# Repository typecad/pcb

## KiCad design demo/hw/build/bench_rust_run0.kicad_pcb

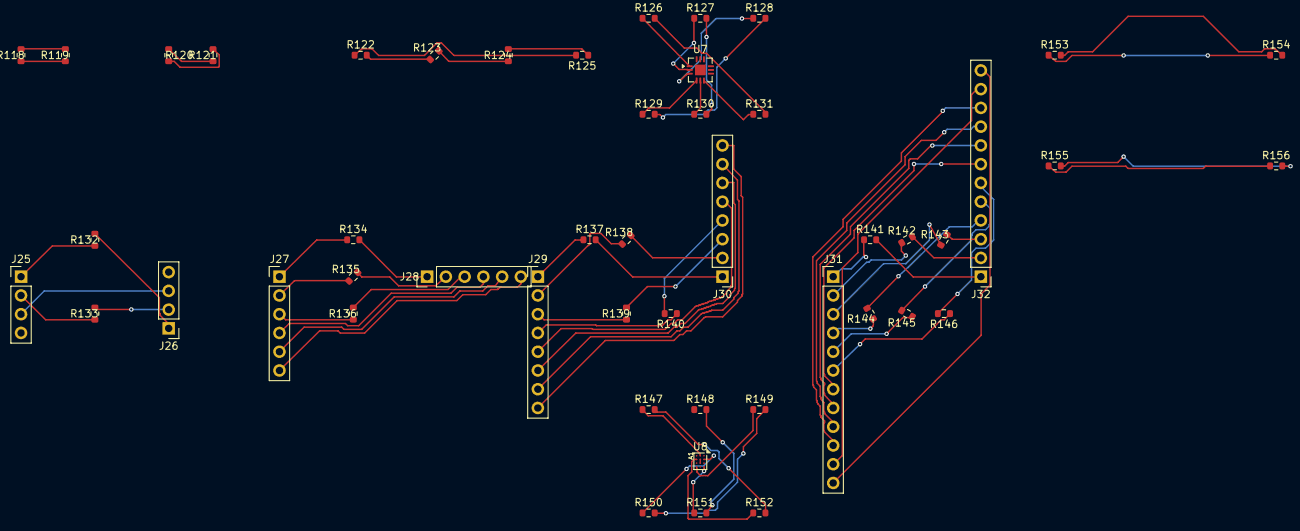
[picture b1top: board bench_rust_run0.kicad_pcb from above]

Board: 0 copper layers, 49 parts (0 on the bottom side), 74 nets.

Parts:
J25, J26: PinHeader_1x04_P2.54mm_Vertical
J27, J28: PinHeader_1x06_P2.54mm_Vertical
J29, J30: PinHeader_1x08_P2.54mm_Vertical
J31, J32: PinHeader_1x12_P2.54mm_Vertical
R118, R119, R120, R121, R122, R123, R124, R125, R126, R127, R128, R129, R130, R131, R132, R133, R134, R135, R136, R137, R138, R139, R140, R141, R142, R143, R144, R145, R146, R147, R148, R149, R150, R151, R152, R153, R154, R155, R156: R_0603_1608Metric
U7: QFN-12-1EP_3x3mm_P0.5mm_EP1.45x1.45mm
U8: Texas_DSBGA-12_1.36x1.86mm_Layout3x4_P0.5mm

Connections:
test1_1: R118.1, R119.1
test1_2: R118.2, R119.2
test2_1: R120.1, R121.1
test2_2: R120.2, R121.2
test3_1: R122.2, R123.1
test3_2: R123.2, R124.1
test3_3: R124.2, R125.1
test3_4: R122.1, R125.2
test4_1: R126.1, U7.1
test4_2: R127.1, U7.2
test4_3: R128.1, U7.3
test4_4: R129.1, U7.4
test4_5: R130.1, U7.5
test4_6: R131.1, U7.6
test4_7: R126.2, R131.2
test4_8: R127.2, R130.2
test4_9: R128.2, R129.2
test5_1: J25.1, R132.1
test5_2: J26.1, R132.2
test5_3: J25.2, R133.1
test5_4: J26.2, R133.2
test5_5: J25.3, J26.3
test6_1: J27.1, R134.1
test6_2: J28.1, R134.2
test6_3: J27.2, R135.1
test6_4: J28.2, R135.2
test6_5: J27.3, R136.1
test6_6: J28.3, R136.2
test6_7: J27.4, J28.4
test6_8: J27.5, J28.5
test6_9: J27.6, J28.6
test7_1: J29.1, R137.1
test7_2: J30.1, R137.2
test7_3: J29.2, R138.1
test7_4: J30.2, R138.2
test7_5: J29.3, R139.1
test7_6: J30.3, R139.2
test7_7: J29.4, R140.1
test7_8: J30.4, R140.2
test7_9: J29.5, J30.5
test7_10: J29.6, J30.6
test7_11: J29.7, J30.7
test7_12: J29.8, J30.8
test8_1: J31.1, R141.1
test8_2: J32.1, R141.2
test8_3: J31.2, R142.1
test8_4: J32.2, R142.2
test8_5: J31.3, R143.1
test8_6: J32.3, R143.2
test8_7: J31.4, R144.1
test8_8: J32.4, R144.2
test8_9: J31.5, R145.1
test8_10: J32.5, R145.2
test8_11: J31.6, R146.1
test8_12: J32.6, R146.2
test8_13: J31.7, J32.7
test8_14: J31.8, J32.8
test8_15: J31.9, J32.9
test8_16: J31.10, J32.10
test8_17: J31.11, J32.11
test8_18: J31.12, J32.12
test9_1: R147.1, U8.A2
test9_2: U8.B2, U8.C2
test9_3: R149.1, U8.D1
test9_4: R150.1, U8.B3
test9_5: R151.1, U8.D3
test9_6: R152.1, U8.B1
test9_7: R147.2, R152.2
test9_8: R148.2, R151.2
test9_9: R149.2, R150.2
test10_1: R153.1, R154.1
test10_2: R153.2, R154.2
test10_3: R155.1, R156.1
test10_4: R155.2, R156.2
